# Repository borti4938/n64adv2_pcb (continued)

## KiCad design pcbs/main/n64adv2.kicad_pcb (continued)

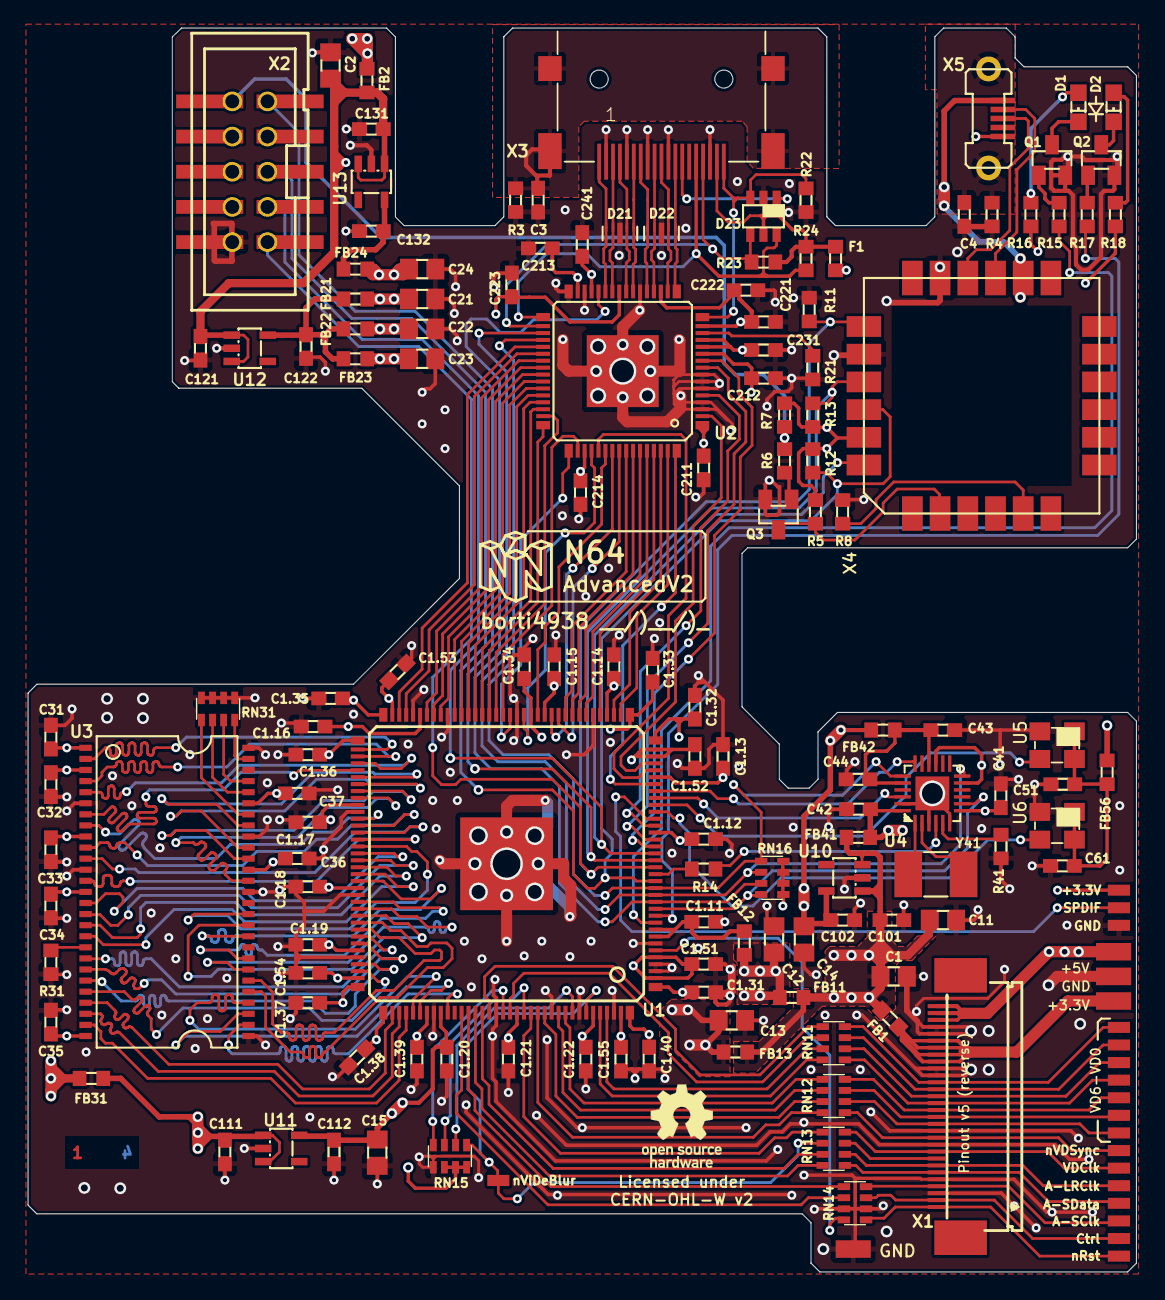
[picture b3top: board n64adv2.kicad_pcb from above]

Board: 4 copper layers, 80.0 x 89.8 mm, 157 parts (0 on the bottom side), 171 nets.

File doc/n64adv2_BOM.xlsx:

Number of PCBs |  | 3
Designator | MPN | QTY/PCB | QTY | DESCRIPTION | VALUE | PACKAGE | NOTES | Digikey | Mouser
U1 | 10M16SAE144 | 1 | 3 | Max10 FPGA, 16k LE |  | EQFP144 | For user
 | 10M25SAE144 |  |  | Max10 FPGA, 25k LE |  | EQFP144 | For developer or as user alternative (more FPGA resources)
U2 | ADV7513BSWZ | 1 | 3 | HDMI Transmitter | ADV7513 | 48-LQFP | Aliexpress
U3 | AS4C8M16SA-xTCN | 1 | 3 | SDRAM Speicher-IC 128 Mb (8 M x 16) Parallel |  | TSOP-54 | x = Speedgrade (6 = 166MHz, 7 = 143MHz)
U4 | SI5356A-B-GMR | 1 | 3 | Clock generator |  | QFN-24
U5 | ECS-3225MV-500-CN-TR | 1 | 3 | OSC 50MHz for system pll |  | 4-SMD | L x B: 0,126" x 0,098" (3,20 mm x 2,50 mm)
U6 | ECS-3225MVLC-245.7-CN-TR | 1 | 3 | OSC 24.576MHz for audio |  | 4-SMD | L x B: 0,126" x 0,098" (3,20 mm x 2,50 mm)
U10 | TLV70225DBVR | 1 | 3 | LDO 2.5V, 300mA |  | SOT-23-5
U11 | TLV70025DDCR | 1 | 3 | LDO 2.5V, 200mA |  | SOT-23-5 | same as U10 can be used (but not vice versa)
 | TLV70225DBVR |  |  | Alternative for U11 (same as U10) |  | SOT-23-5
U12 | TLV70218DBVR | 1 | 3 | LDO 1.8V |  | SOT-23-5
U13 | TLV70033DDCR | 1 | 3 | LDO 3.3V |  | SOT-23-5
Y41 | 445I23D27M00000 | 1 | 3 | 27MHz crystal |  | 5.0X3.2
FB1,FB2,FB11,FB12,FB13,FB21,FB22,FB23,FB24,FB31,FB41,FB42,FB56 | MPZ1608S221A | 13 | 39 | Ferrit bead, power line |  | SMD0603
C1,C2 | ‎GRT21BR60J476ME13L‎ | 2 | 6 | Ceramic capacitor, X5R | 47uF / 6.3V | SMD0805
C11,C12,C13,C14,C15,C21,C22,C23,C24 | ‎CL21A106KPFNNNG‎ | 9 | 27 | Ceramic capacitor, X5R | 10uF / 6.3V | SMD0805
C101,C102,C111,C112,C121,C122,C131,C132 | ‎CL10A105KP8NNWC‎ | 8 | 24 | Ceramic capacitor, X5R | 1uF / 6.3V | SMD0603
C1.11,C1.12,C1.13,C1.14,C1.15,C1.16,C1.17,C1.18,C1.19,C1.20,C1.21,C1.22,C1.31,C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 | CL10B104KB8NNNL | 48 | 144 | Ceramic capacitor, X7R | 0.1uF / 50V | SMD0603
C51,C61 | CL10B103KB8NNNC | 2 | 6 | Ceramic capacitor, X7R | 0.01uF / 50V | SMD0603
R3 | RC0603FR-071ML | 1 | 3 | Resistor | 1M | SMD0603
R12,R13,R22 | RC0603FR-0710KL | 3 | 9 | Resistor | 10k | SMD0603
R23,R24 | RC0603FR-072KL | 2 | 6 | Resistor | 2k0 | SMD0603
R11,R15,R17,R31,R41 | RC0603FR-071KL | 5 | 15 | Resistor | 1k0 | SMD0603
R21 | RC0603FR-07887RL | 1 | 3 | Resistor | 887 | SMD0603
R16,R18 | RC0603FR-07330RL | 2 | 6 | Resistor | 330 | SMD0603
R14 | RC0603FR-0733RL | 1 | 3 | Resistor | 33 | SMD0603
RN11,RN12,RN13,RN14 | BLA31AG121SN4D | 4 | 12 | Ferrite Beads MULTILYR CHP | BD 120OHMS 25% | SMD1206
RN15,RN31 | CAY16-103J4LF | 2 | 6 | Resistor Array (4x) | 10k0 | SMD1206
RN16 | CAY16-2201F4LF | 1 | 3 | Resistor Array (4x) | 2k2 | SMD1206
F1 | MF-FSMF020X-2 | 1 | 3 | 200mA Fuse |  | SMD0603
D1 | LTST-C194KRKT | 1 | 3 | Red LED |  | SMD0805
D2 | LTST-C194KGKT | 1 | 3 | Green LED |  | SMD0805
 | LTST-C194KRKT |  |  | Alternative for D2 (same as D1) |  | SMD0805
D21,D22 | RCLAMP0524PATCT | 2 | 6 | TVS Diode |  | 10-UFDFN
 | SZESD7104MUTAG |  |  | TVS Diode |  | 10-UFDFN | Alternative
D23 | NUP4114HMR6T1G | 1 | 3 | Clamping Diode Array |  | TSOP-6
Q1,Q2 | ZXTN08400BFFTA | 2 | 6 | NPN-Transistor |  | SOT-23
X1 | 3-1734592-0 | 1 | 3 | contacts bottom, cable 0.3mm thick (flex + stiffener) |  |  | 30 pin 0.5mm flat cable connector, reverse v5 pinout, 5V & 3.3V power rail, GND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
 |  |  |  |  |  |  | only in combination with flex (see separate tab)
X2 | 3020-10-0300-00 | 1 | 3 |  |  |  | JTAG Connector (2x5 pins in 100mil pitch; SMD)
 | 30310-6002HB |  |  | Alternative for X2 as THT, but need to short pins |  |  | JTAG Connector (2x5 pins in 100mil pitch; THT)
 |  |  |  |  |  |  | optional if onboard USB Blaster is used (see separate tab)
X3 | 2000-1-2-41-00-BK | 1 | 3 | HDMI Connector 19pin with SMD mounted shield |  |  | Full Size HDMI Connector
X4 | Onboard USB Blaster |  |  |  |  |  | see Onboard USB Blaster page

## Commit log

2021-11-14 initial commit new repository
2021-11-14 add full custom flex RCP to N64Adv2
2022-02-14 update JTAG spacer
2022-04-18 huge update: - I know: commit is too large - port main PCB to KiCad - reorganize repo structure - add README
2022-04-18 some typos
2022-04-18 add UltraPIF description
2022-07-22 update full flex: - redesign in KiCad - add trace for VI-DeBlur Feedback
2022-08-23 update flex PCB with minor changes, e.g. added a logo
2022-08-23 update main PCB with minor changes, e.g. ensure that solder mask bridges between 0.5mm pitched pads has min. 0.1mm thickness
2022-08-23 add PCB specs to README
2022-08-23 update common BOM
2022-09-05 update flex PCB: - add a feedback path for VI-Deblur - optimize implementation around U1 - add logo and license text to silkscreen
2022-09-05 add a small remark that fw needs adaptation for 16Mx16 SDRAM usage
2022-09-05 update main PCB: - optimize some trace routing - optimize component selection/placing (e.g. HDMI port full SMD, JTAG as SMD alternative) - add license to silkscreen
2022-09-05 update full BOM
2022-09-05 add changelog and license
2022-09-14 Main PCB update: - edge cuts: yet another update hopefully getting the perfect fit this time - hdmi connector position moved 0.5mm to the left - optimize mask for D21, D22, X3
2022-10-09 tiny optimizations: - change HDMI footprint a bit (increase size of shield pads) - move HDMI port a bit further on the PCB - adapt copper pour on l2 a bit
2022-11-06 reduce pad hole size at usb port and fix a gnd trace
2022-11-06 update gerbers
2022-11-12 update 3d printed models for new HDMI port
2022-11-12 update names for 3D printed parts
2022-11-20 give a bit mor space at the MultiOut stand-offs as earliest N64 models (PAL only???) seems to have thicker ones there
2022-11-20 some BOM updates
2022-12-01 fix edge cuts problem and rearrange some power supply lines near HDMI Tx
2023-05-21 update part numbers for Y41,, RN11-14
2023-11-05 update main-pcb: - remove jumper which were left overs from prototype stages - remove some test points - add pads for SPDIF near DIY-IO-Pad area
2023-11-05 Update flex-PCB: - move buffer IC to resistor array area of PCB (not on arms anymore) - add pads as backup if arms get ripped off
2023-11-26 Update main-PCB: - fixing solder mask - slightly move components a bit (USB port, JTAG, C2, ...)
2023-11-26 Update BOM
2023-11-27 protect unconnected pad at U1 by small traces
2024-01-20 leave a note and BOM for the PicoDVI-N64_PCB project by dalogue1
2024-08-08 remove BOM for PicoDVI
2024-08-08 Adjust BOM a tiny bit
2024-08-16 remove left over note
